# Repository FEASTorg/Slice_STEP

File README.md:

<div align="center">
  <!-- Title: -->
  
  <h2><a href="https://github.com/uwo-fast/Slice_STEP"> STEP Slice </a></h2>
  <!-- Labels: -->
  <!-- First row: -->

  <a href="https://certification.oshwa.org/">
    
    <!-- img src="https://img.shields.io/badge/OSHWA-Certified-darkgreen?style=flat-square" height="20" alt="OSHWA" -->       <!-- img src="https://img.shields.io/badge/OSHWA-Pending-darkorange?style=flat-square" height="20" alt="OSHWA" -->
  </a>

  <!-- Second row: -->
  <br>

  <!-- Short description: -->
  <h3>Stepper Motor Driver Carrier Slice for BREAD.</h3>
</div>

## Introduction
[Provide a brief introduction to the project, including the motivation and goals. Explain the significance and context of the research.]

## Project Overview
[Describe the project in more detail. This section can be split into subsections if necessary.]

## Installation
[Provide instructions for installing any necessary software or hardware components.]

## Usage
[Explain how to use the project. Include examples and screenshots if applicable.]

### Basic Usage
[Provide basic usage instructions.]

### Advanced Usage
[Provide advanced usage instructions, including any optional features or configurations.]

## Documentation
[Link to the detailed documentation if available. Provide instructions on how to access and navigate the documentation.]

## Contributing
[Explain how others can contribute to the project. Include guidelines for submitting issues, pull requests, and any coding standards.]

### Code of Conduct
[Link to the project's code of conduct if available.]

## License
[State the license under which the project is distributed. Include a link to the full license text.]

## Acknowledgements
[Acknowledge any contributors, collaborators, funding sources, or organizations that supported the project.]

## Contact
[Provide contact information for the project maintainer(s) or lead researcher(s). Include an email address or a link to a contact form.]

---

<div align="center">
  
</div>

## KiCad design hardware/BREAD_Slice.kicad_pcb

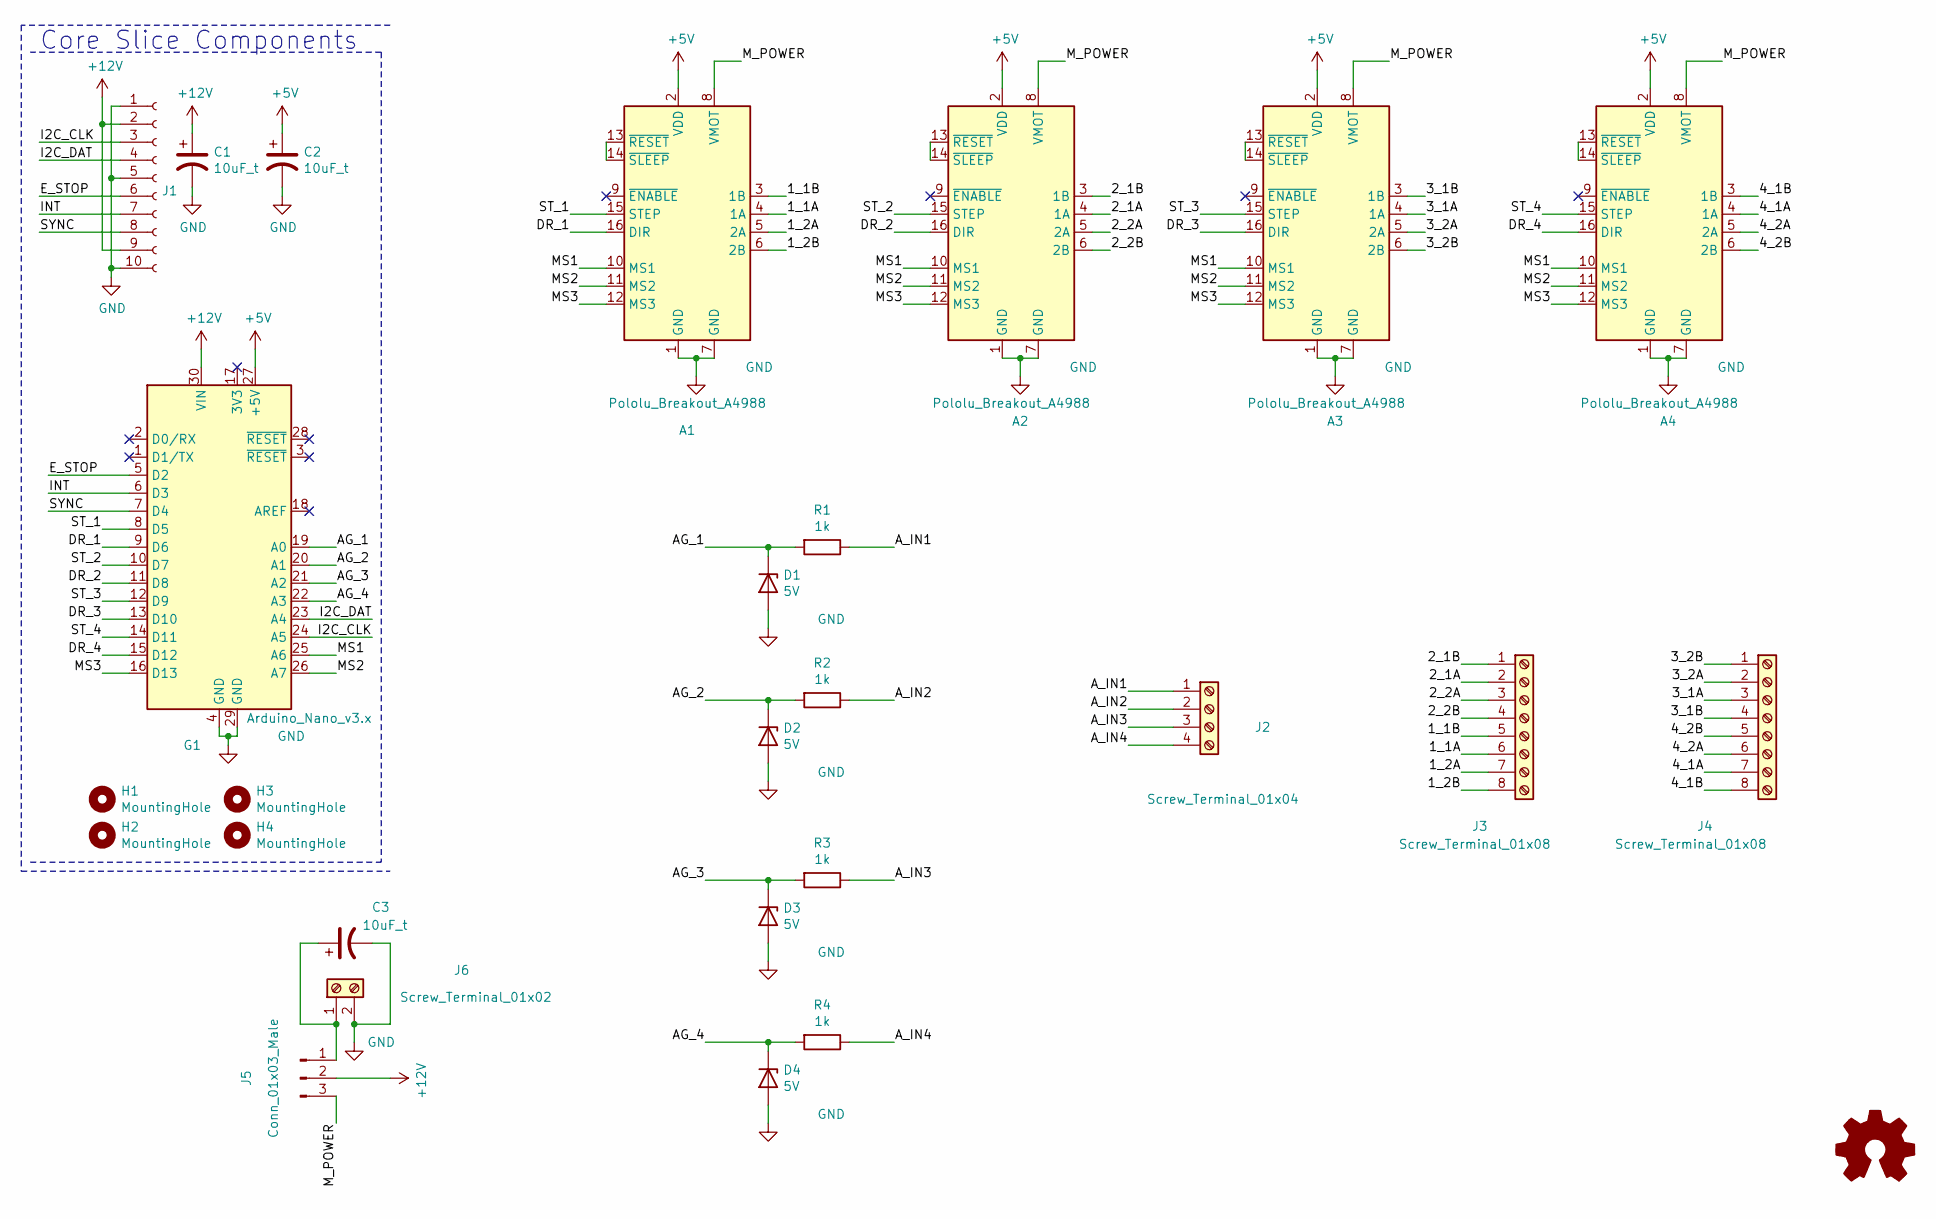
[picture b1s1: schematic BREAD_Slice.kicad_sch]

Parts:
A1, A2, A3, A4: Pololu_Breakout_A4988; Pololu_Breakout-16_15.2x20.3mm
C1, C2, C3: 10uF_t; C_2312; Part # T491C106K025AT
D1, D2, D3, D4: 5V; D_1206_3216Metric_Pad1.42x1.75mm_HandSolder
G1: Arduino_Nano_v3.x; Arduino_Nano
H1, H2, H3, H4: MountingHole; MountingHole_3.2mm_M3_DIN965_Pad
J1: Conn_01x10_Female; PinSocket_1x10_P2.54mm_Horizontal
J2: Screw_Terminal_01x04; TerminalBlock_TE_282834-4_1x04_P2.54mm_Horizontal
J3, J4: Screw_Terminal_01x08; TerminalBlock_TE_282834-8_1x08_P2.54mm_Horizontal
J5: Conn_01x03_Male; PinSocket_1x03_P2.54mm_Vertical
J6: Screw_Terminal_01x02; TerminalBlock_TE_282834-2_1x02_P2.54mm_Horizontal
Logo1: Logo_Open_Hardware_Small; OSHW-Symbol_6.7x6mm_SilkScreen
R1, R2, R3, R4: 1k; R_1206_3216Metric_Pad1.30x1.75mm_HandSolder

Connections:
+5V: A1.2 (VDD), A2.2 (VDD), A3.2 (VDD), A4.2 (VDD), C2.1, G1.27 (+5V)
+12V: C1.1, G1.30 (VIN), J1.2, J1.9, J5.2
/1_1A: A1.4 (1A), J3.6
/1_1B: A1.3 (1B), J3.5
/1_2A: A1.5 (2A), J3.7
/1_2B: A1.6 (2B), J3.8
/2_1A: A2.4 (1A), J3.2
/2_1B: A2.3 (1B), J3.1
/2_2A: A2.5 (2A), J3.3
/2_2B: A2.6 (2B), J3.4
/3_1A: A3.4 (1A), J4.3
/3_1B: A3.3 (1B), J4.4
/3_2A: A3.5 (2A), J4.2
/3_2B: A3.6 (2B), J4.1
/4_1A: A4.4 (1A), J4.7
/4_1B: A4.3 (1B), J4.8
/4_2A: A4.5 (2A), J4.6
/4_2B: A4.6 (2B), J4.5
/AG_1: D1.1 (K), G1.19 (A0), R1.2
/AG_2: D2.1 (K), G1.20 (A1), R2.2
/AG_3: D3.1 (K), G1.21 (A2), R3.2
/AG_4: D4.1 (K), G1.22 (A3), R4.2
/A_IN1: J2.1, R1.1
/A_IN2: J2.2, R2.1
/A_IN3: J2.3, R3.1
/A_IN4: J2.4, R4.1
/DR_1: A1.16 (DIR), G1.9 (D6)
/DR_2: A2.16 (DIR), G1.11 (D8)
/DR_3: A3.16 (DIR), G1.13 (D10)
/DR_4: A4.16 (DIR), G1.15 (D12)
/E_STOP: G1.5 (D2), J1.6
/I2C_CLK: G1.24 (A5), J1.3
/I2C_DAT: G1.23 (A4), J1.4
/INT: G1.6 (D3), J1.7
/MS1: A1.10 (MS1), A2.10 (MS1), A3.10 (MS1), A4.10 (MS1), G1.25 (A6)
/MS2: A1.11 (MS2), A2.11 (MS2), A3.11 (MS2), A4.11 (MS2), G1.26 (A7)
/MS3: A1.12 (MS3), A2.12 (MS3), A3.12 (MS3), A4.12 (MS3), G1.16 (D13)
/M_POWER: A1.8 (VMOT), A2.8 (VMOT), A3.8 (VMOT), A4.8 (VMOT), J5.3
/ST_1: A1.15 (STEP), G1.8 (D5)
/ST_2: A2.15 (STEP), G1.10 (D7)
/ST_3: A3.15 (STEP), G1.12 (D9)
/ST_4: A4.15 (STEP), G1.14 (D11)
/SYNC: G1.7 (D4), J1.8
GND: A1.1 (GND), A1.7 (GND), A2.1 (GND), A2.7 (GND), A3.1 (GND), A3.7 (GND), A4.1 (GND), A4.7 (GND), C1.2, C2.2, C3.2, D1.2 (A), D2.2 (A), D3.2 (A), D4.2 (A), G1.4 (GND), G1.29 (GND), J1.1, J1.5, J1.10, J6.2
unnamed: A1.13 (~RESET), A1.14 (~SLEEP)
unnamed: A2.13 (~RESET), A2.14 (~SLEEP)
unnamed: A3.13 (~RESET), A3.14 (~SLEEP)
unnamed: A4.13 (~RESET), A4.14 (~SLEEP)
unnamed: C3.1, J5.1, J6.1

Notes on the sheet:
Core Slice Components

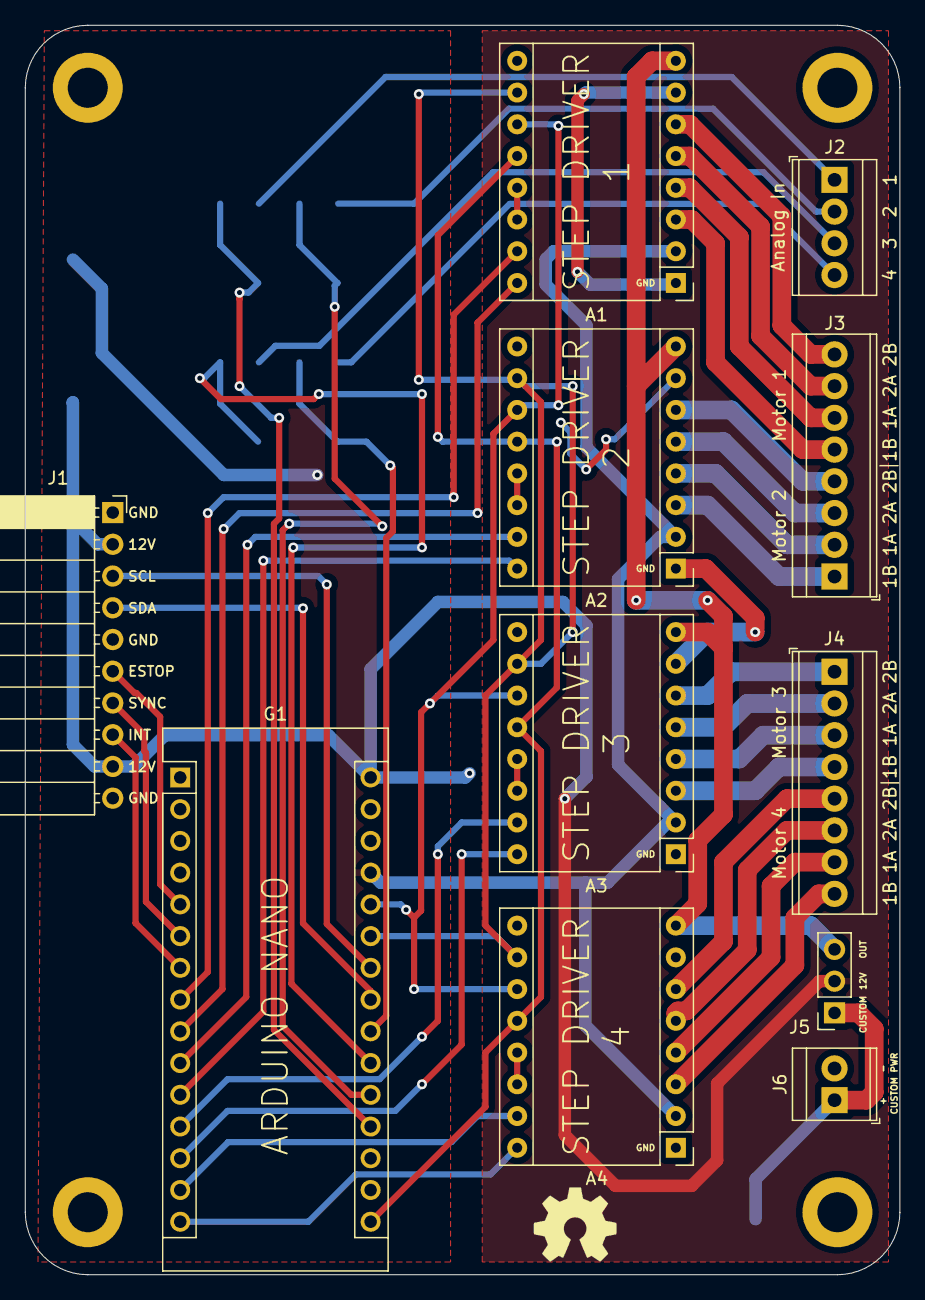
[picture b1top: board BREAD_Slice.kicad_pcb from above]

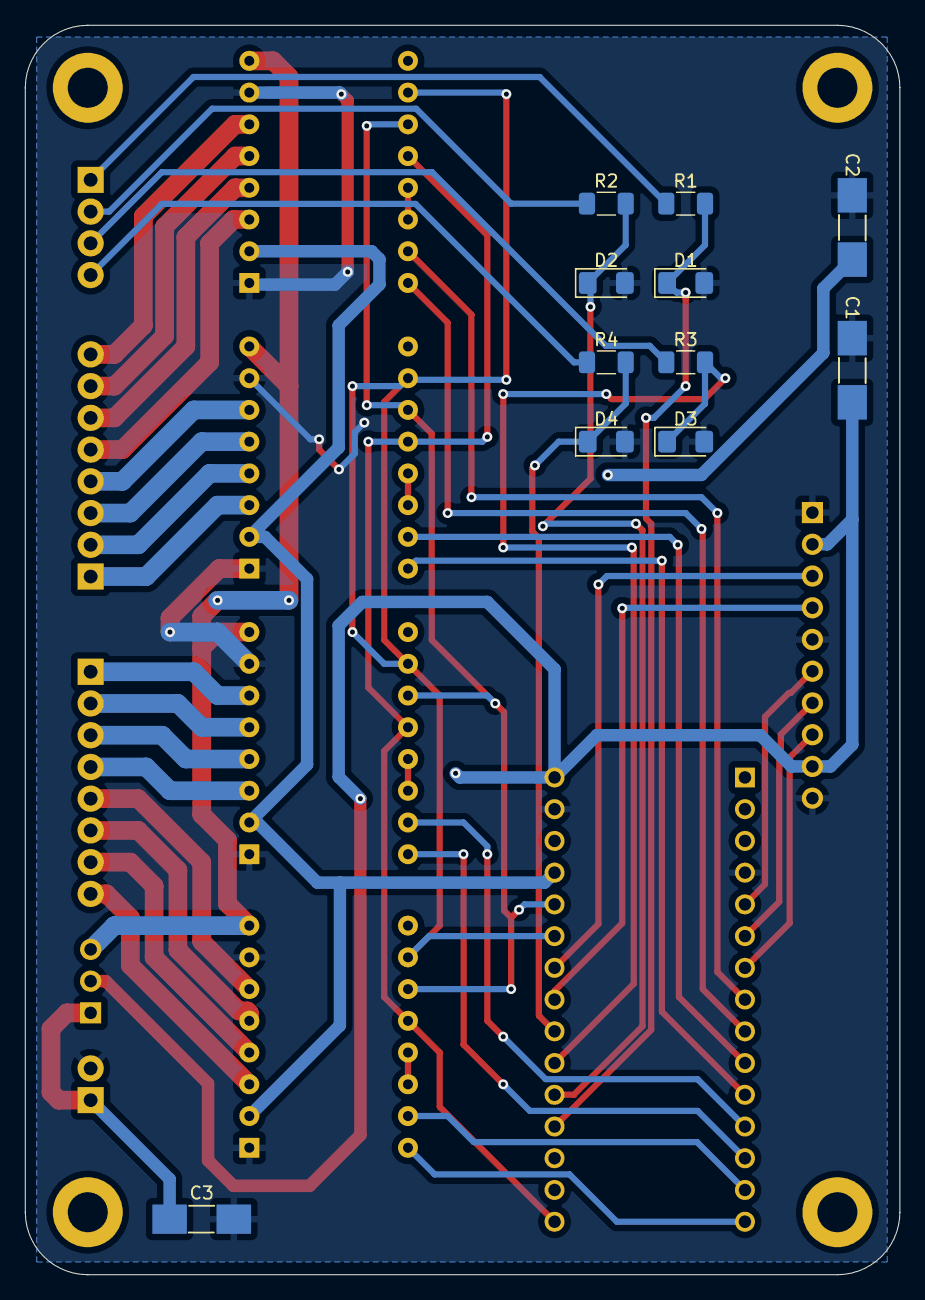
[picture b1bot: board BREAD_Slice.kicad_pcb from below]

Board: 2 copper layers, 70.0 x 100.0 mm, 27 parts (11 on the bottom side), 49 nets.

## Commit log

2024-05-23 Initial commmit
2025-04-19 minor tweaks
2026-04-18 chore: revisions to step board
2026-05-20 Add slice.yaml manifest (schema v1.0)
2026-05-24 Add KiBot/docs pipeline
2026-05-24 Update TODO with CI findings
2026-05-24 Standardize TODO.md with Pass 1/Pass 2 structure
